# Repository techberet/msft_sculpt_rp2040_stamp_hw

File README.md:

# msft_sculpt_rp2040_stamp_hw

Lots of details available in my (rather long) [blog post](https://techberet.com/2024/09/07/replacement-pcb-for-sculpt-rp2040).

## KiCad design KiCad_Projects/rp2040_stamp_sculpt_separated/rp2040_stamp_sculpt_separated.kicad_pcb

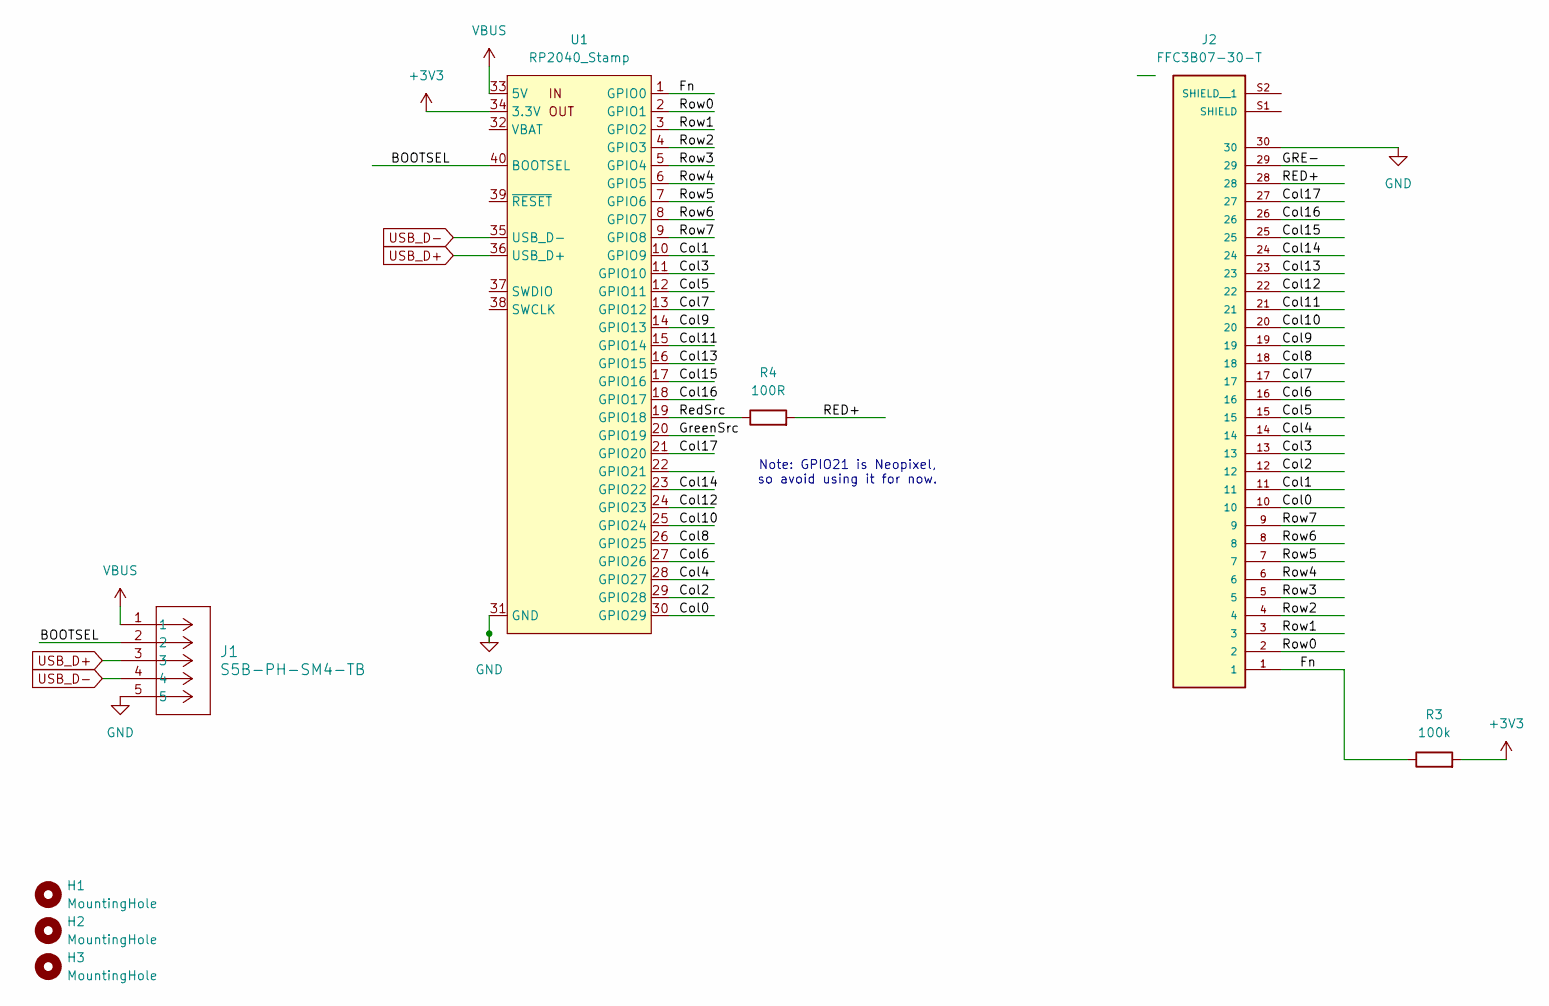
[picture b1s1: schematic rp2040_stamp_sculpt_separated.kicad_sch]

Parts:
H1, H2: MountingHole; MountingHole_2.2mm_M2
H3: MountingHole; MountingHole_2.7mm
J1: S5B-PH-SM4-TB; S5B_PH_SM4_TB
J2: FFC3B07-30-T; FFC3B07_30_T; PARTREV A
R3: 100k; R_1206_3216Metric_Pad1.30x1.75mm_HandSolder
R4: 100R; R_1206_3216Metric_Pad1.30x1.75mm_HandSolder
U1: RP2040_Stamp

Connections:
+3V3: R3.2, U1.34 (3.3V)
/BOOTSEL: J1.2, U1.40 (BOOTSEL)
/Col0: J2.10, U1.30 (GPIO29)
/Col1: J2.11, U1.10 (GPIO9)
/Col2: J2.12, U1.29 (GPIO28)
/Col3: J2.13, U1.11 (GPIO10)
/Col4: J2.14, U1.28 (GPIO27)
/Col5: J2.15, U1.12 (GPIO11)
/Col6: J2.16, U1.27 (GPIO26)
/Col7: J2.17, U1.13 (GPIO12)
/Col8: J2.18, U1.26 (GPIO25)
/Col9: J2.19, U1.14 (GPIO13)
/Col10: J2.20, U1.25 (GPIO24)
/Col11: J2.21, U1.15 (GPIO14)
/Col12: J2.22, U1.24 (GPIO23)
/Col13: J2.23, U1.16 (GPIO15)
/Col14: J2.24, U1.23 (GPIO22)
/Col15: J2.25, U1.17 (GPIO16)
/Col16: J2.26, U1.18 (GPIO17)
/Col17: J2.27, U1.21 (GPIO20)
/Fn: J2.1, R3.1, U1.1 (GPIO0)
/GRE-: J2.29
/GreenSrc: U1.20 (GPIO19)
/RED+: J2.28, R4.2
/RedSrc: R4.1, U1.19 (GPIO18)
/Row0: J2.2, U1.2 (GPIO1)
/Row1: J2.3, U1.3 (GPIO2)
/Row2: J2.4, U1.4 (GPIO3)
/Row3: J2.5, U1.5 (GPIO4)
/Row4: J2.6, U1.6 (GPIO5)
/Row5: J2.7, U1.7 (GPIO6)
/Row6: J2.8, U1.8 (GPIO7)
/Row7: J2.9, U1.9 (GPIO8)
GND: J1.5, J2.30, U1.31 (GND)
USB_D+: J1.3, U1.36 (USB_D+)
USB_D-: J1.4, U1.35 (USB_D-)
VBUS: J1.1, U1.33 (5V)

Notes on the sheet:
Note: GPIO21 is Neopixel, so avoid using it for now.

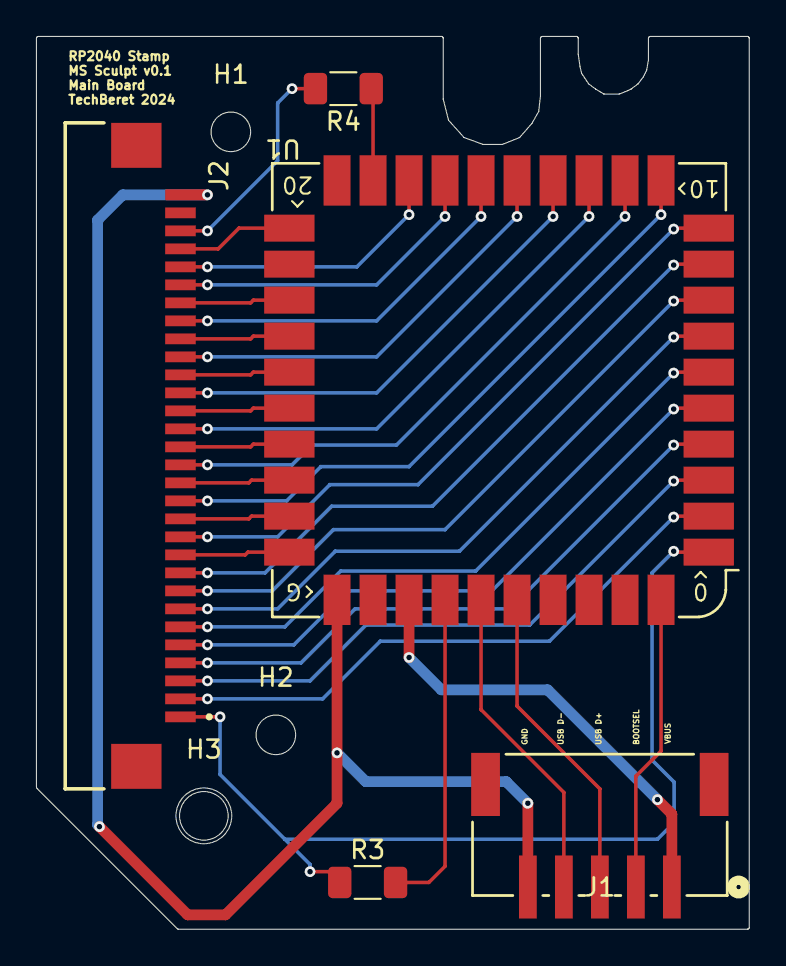
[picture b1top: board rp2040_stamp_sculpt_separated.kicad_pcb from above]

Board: 2 copper layers, 39.6 x 49.6 mm, 8 parts (0 on the bottom side), 35 nets.

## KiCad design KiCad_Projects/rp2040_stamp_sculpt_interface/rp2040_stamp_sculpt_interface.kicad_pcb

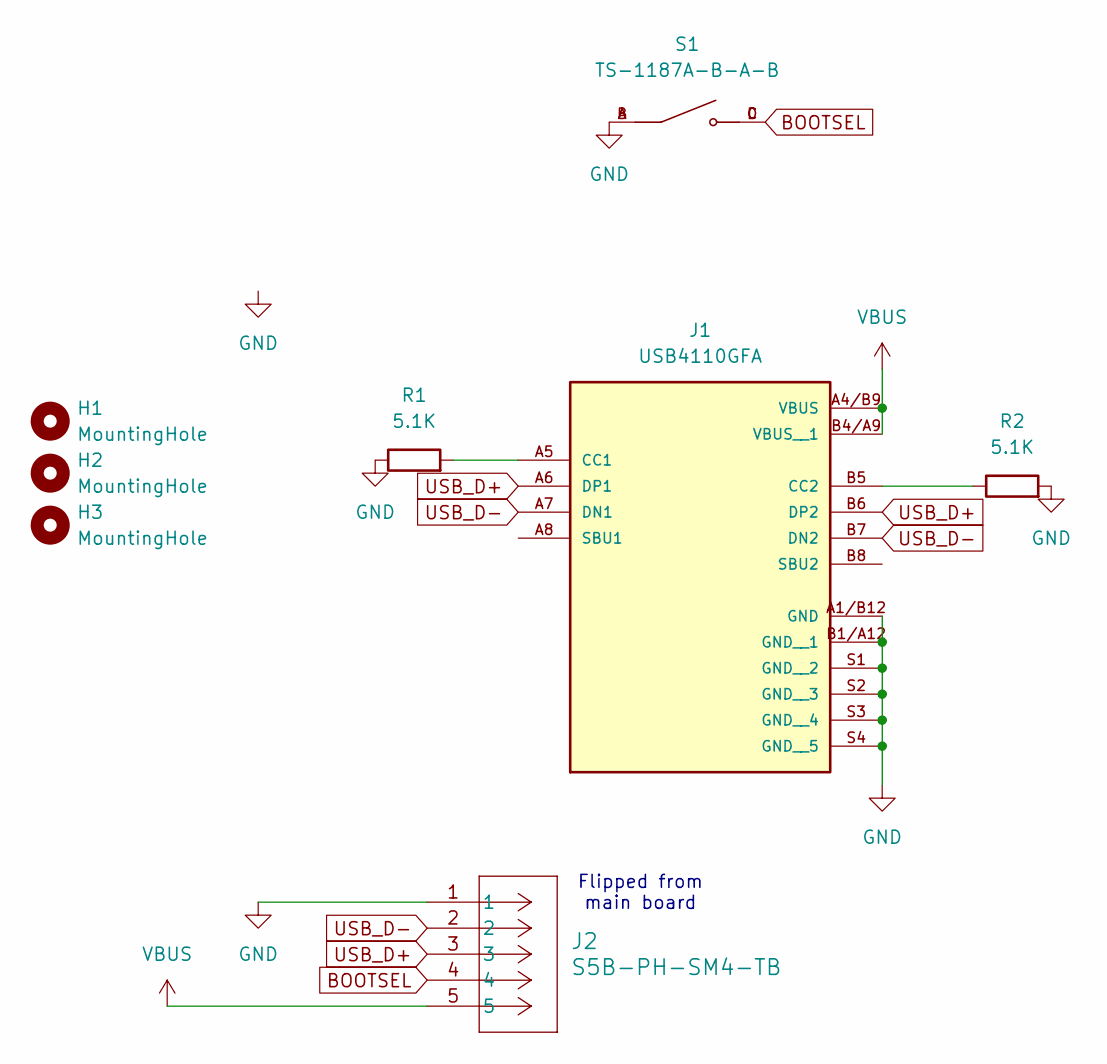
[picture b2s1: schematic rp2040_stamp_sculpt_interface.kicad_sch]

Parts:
H1, H2, H3: MountingHole; MountingHole_2.2mm_M2
J1: USB4110GFA; USB4110_GF_A
J2: S5B-PH-SM4-TB; S5B_PH_SM4_TB
R1, R2: 5.1K; R_1206_3216Metric_Pad1.30x1.75mm_HandSolder
S1: TS-1187A-B-A-B; TS_1187A_B_A_B; PARTREV A0

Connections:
BOOTSEL: J2.4, S1.C, S1.D
GND: J1.A1/B12 (GND), J1.B1/A12 (GND__1), J1.S1 (GND__2), J1.S2 (GND__3), J1.S3 (GND__4), J1.S4 (GND__5), J2.1, R1.1, R2.2, S1.A, S1.B
unnamed: J1.A5 (CC1), R1.2
unnamed: J1.B5 (CC2), R2.1
USB_D+: J1.A6 (DP1), J1.B6 (DP2), J2.3
USB_D-: J1.A7 (DN1), J1.B7 (DN2), J2.2
VBUS: J1.A4/B9 (VBUS), J1.B4/A9 (VBUS__1), J2.5

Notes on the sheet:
Flipped from main board

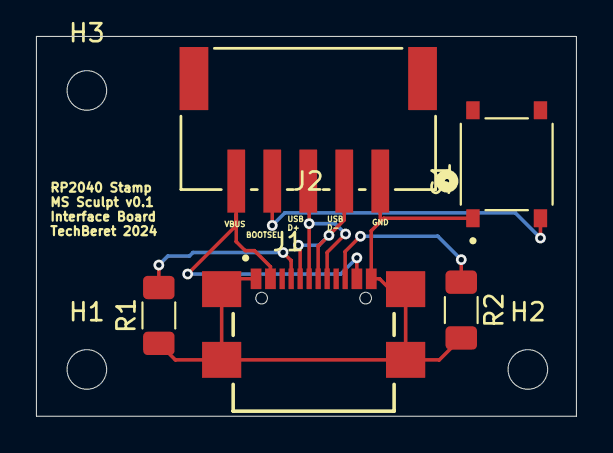
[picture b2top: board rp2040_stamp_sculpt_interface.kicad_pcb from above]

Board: 2 copper layers, 30.0 x 21.1 mm, 8 parts (0 on the bottom side), 7 nets.

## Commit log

2024-08-27 Initial commit of both KiCAD and OpenSCAD projects for blog post.
2024-09-07 Add link to blog post to README.
